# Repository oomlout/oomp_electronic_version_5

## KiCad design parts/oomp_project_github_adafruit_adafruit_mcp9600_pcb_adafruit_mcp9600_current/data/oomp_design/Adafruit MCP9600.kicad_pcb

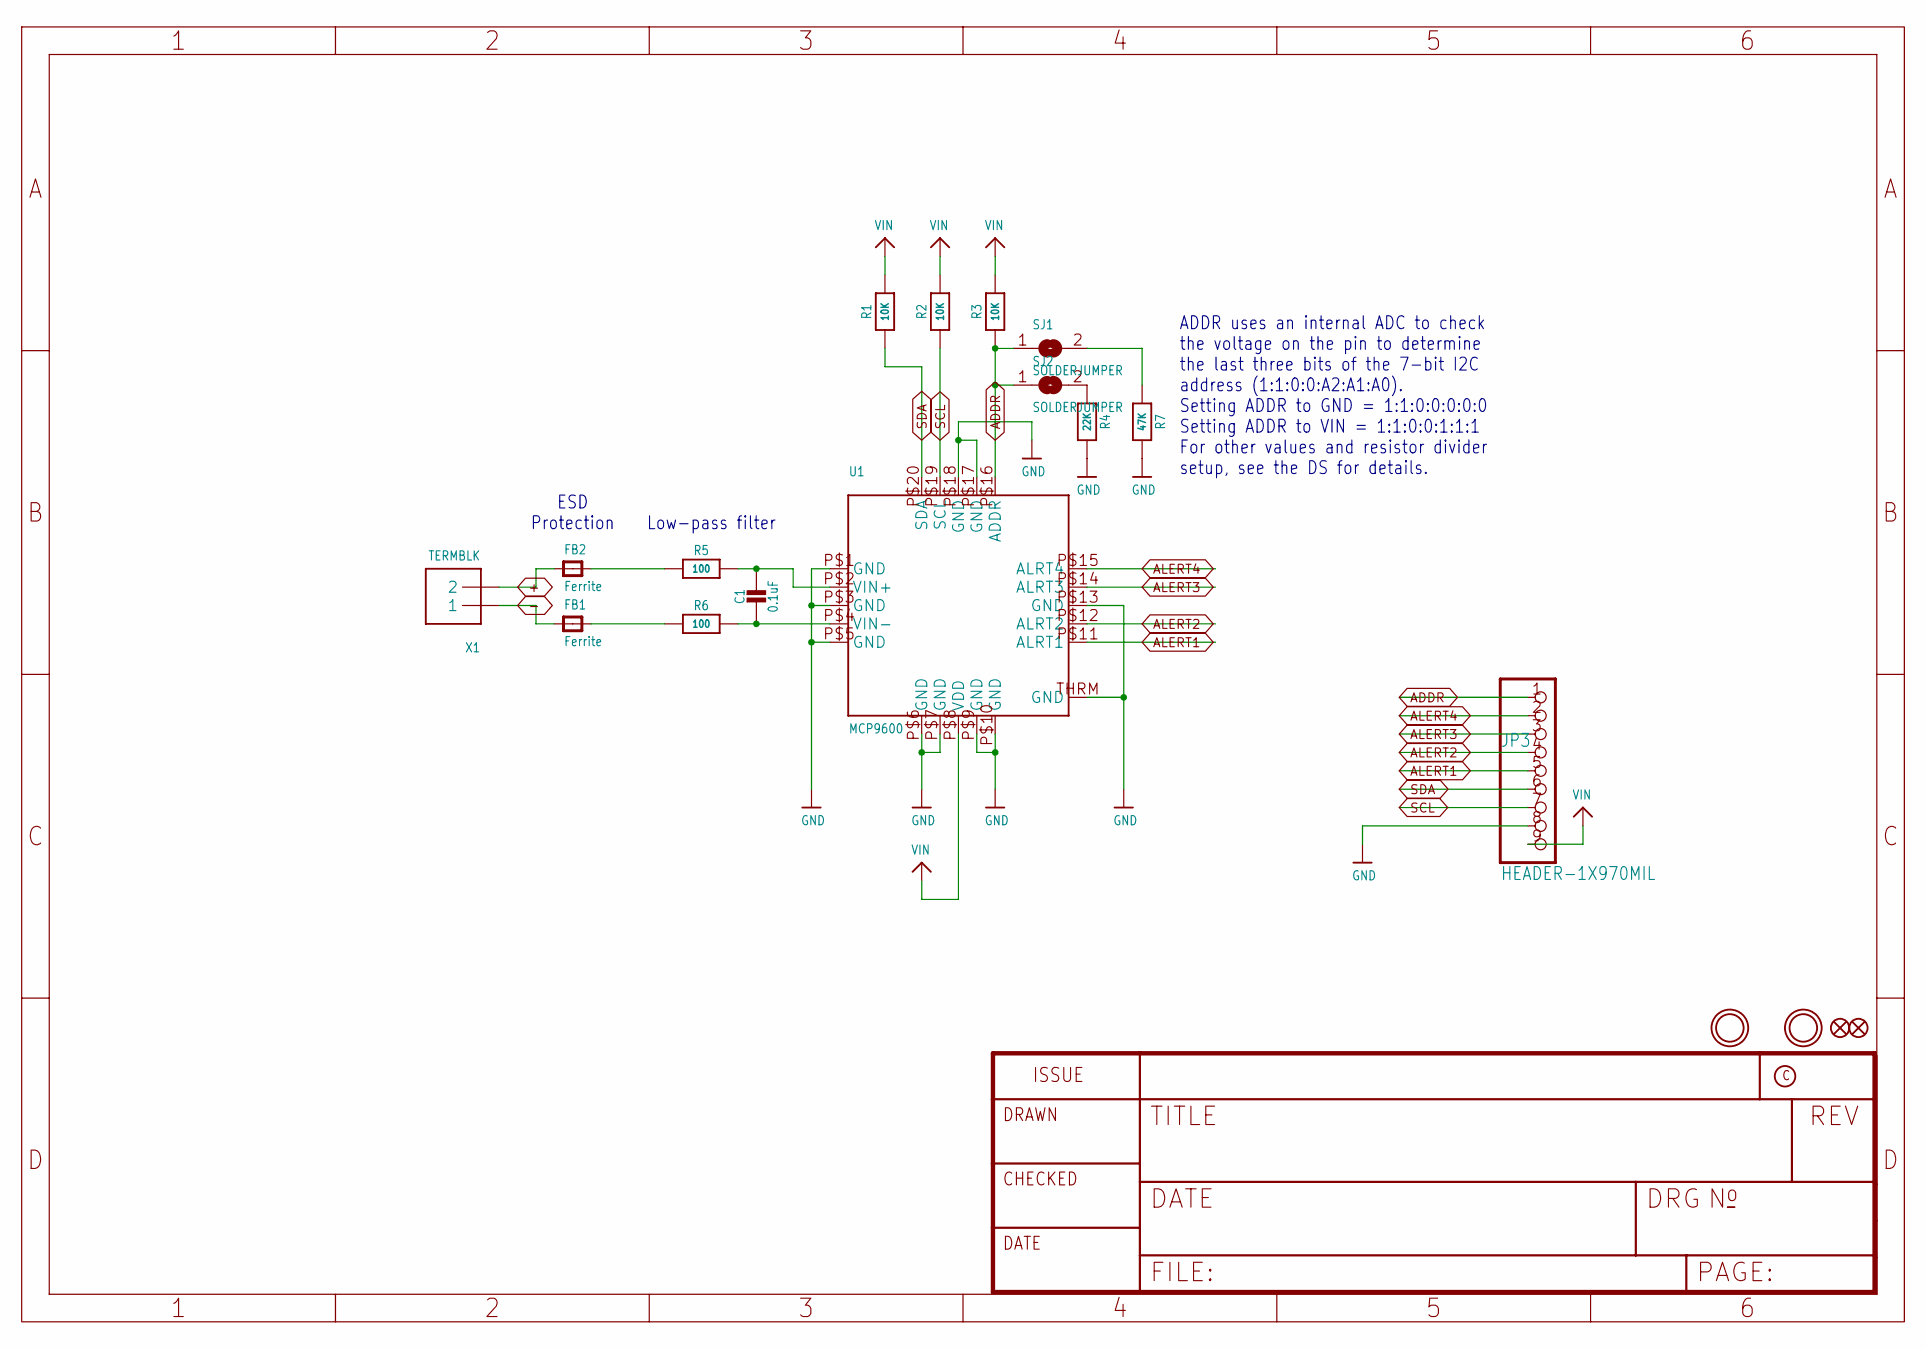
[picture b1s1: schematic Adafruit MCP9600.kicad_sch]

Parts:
C1: 0.1uF; 0603-NO
FB1, FB2: Ferrite; 0805-NO
FID1, FID2: FIDUCIAL_1MM
JP3: HEADER-1X970MIL; 1X09_ROUND_70
R1, R2, R3: 10K; 0603-NO
R4: 22K; 0603-NO
R5, R6: 100; 0603-NO
R7: 47K; 0603-NO
SJ1, SJ2: SOLDERJUMPER; SOLDERJUMPER_ARROW_NOPASTE
U1: MCP9600; VQFN20_5MM
U$1, U$3: MOUNTINGHOLE2.5; MOUNTINGHOLE_2.5_PLATED
X1: TERMBLK; TERMBLOCK_1X2-3.5MM

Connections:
+: FB2.1, X1.2
-: FB1.1, X1.1
ADDR: JP3.1, R3.1, SJ1.1, SJ2.1, U1.P$16 (ADDR)
ALERT1: JP3.5, U1.P$11 (ALRT1)
ALERT2: JP3.4, U1.P$12 (ALRT2)
ALERT3: JP3.3, U1.P$14 (ALRT3)
ALERT4: JP3.2, U1.P$15 (ALRT4)
GND: JP3.8, R4.2, R7.2, U1.P$1 (GND), U1.P$3 (GND), U1.P$5 (GND), U1.P$6 (GND), U1.P$7 (GND), U1.P$9 (GND), U1.P$10 (GND), U1.P$13 (GND), U1.P$17 (GND), U1.P$18 (GND), U1.THRM (GND)
unnamed: C1.1, R5.2, U1.P$2 (VIN+)
unnamed: C1.2, R6.2, U1.P$4 (VIN-)
unnamed: FB1.2, R6.1
unnamed: FB2.2, R5.1
unnamed: R7.1, SJ1.2
unnamed: R4.1, SJ2.2
SCL: JP3.7, R2.1, U1.P$19 (SCL)
SDA: JP3.6, R1.1, U1.P$20 (SDA)
VIN: JP3.9, R1.2, R2.2, R3.2, U1.P$8 (VDD)

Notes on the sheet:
ESD Protection
ADDR uses an internal ADC to check the voltage on the pin to determine the last three bits of the 7-bit I2C address (1:1:0:0:A2:A1:A0). Setting ADDR to GND = 1:1:0:0:0:0:0 Setting ADDR to VIN = 1:1:0:0:1:1:1 For other values and resistor divider setup, see the DS for details.
Low-pass filter

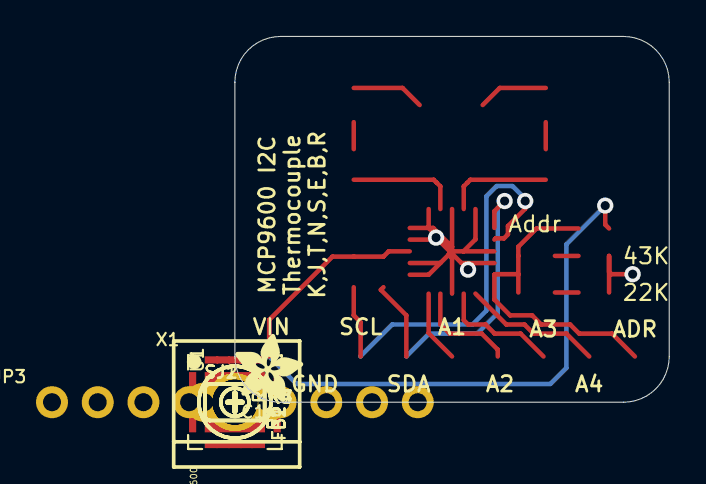
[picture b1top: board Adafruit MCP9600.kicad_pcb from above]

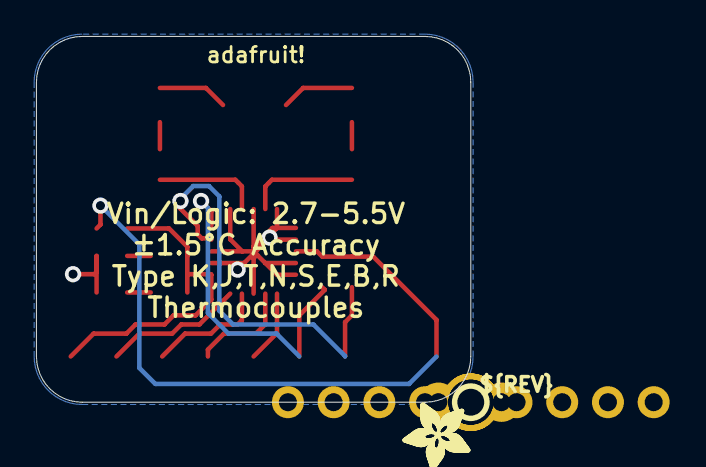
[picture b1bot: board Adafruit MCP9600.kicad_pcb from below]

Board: 2 copper layers, 24.1 x 20.3 mm, 25 parts (3 on the bottom side), 17 nets.

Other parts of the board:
U$16, U$19, U$20: ADAFRUIT_3.5MM
U$17: SYMBOL_PLUS
U$18: SYMBOL_MINUS
U$21: PCBFEAT-REV-040

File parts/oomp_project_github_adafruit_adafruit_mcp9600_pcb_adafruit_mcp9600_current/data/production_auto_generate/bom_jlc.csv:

Comment,Designator,Footprint,LCSC Part #
,JP3,Adafruit MCP9600-import-fps:1X09_ROUND_70,C2932701
,"U$16,U$19,U$20",Adafruit MCP9600-import-fps:ADAFRUIT_3.5MM,
,U$21,Adafruit MCP9600-import-fps:PCBFEAT-REV-040,
,U$18,Adafruit MCP9600-import-fps:SYMBOL_MINUS,
,U$17,Adafruit MCP9600-import-fps:SYMBOL_PLUS,
0.1uF,C1,Adafruit MCP9600-import-fps:0603-NO,C14663
100,"R5,R6",Adafruit MCP9600-import-fps:0603-NO,C22775
10K,"R1,R2,R3",Adafruit MCP9600-import-fps:0603-NO,C98220
22K,R4,Adafruit MCP9600-import-fps:0603-NO,C31850
47K,R7,Adafruit MCP9600-import-fps:0603-NO,C2907042
Ferrite,"FB1,FB2",Adafruit MCP9600-import-fps:0805-NO,
MCP9600,U1,Adafruit MCP9600-import-fps:VQFN20_5MM,
TERMBLK,X1,Adafruit MCP9600-import-fps:TERMBLOCK_1X2-3.5MM,

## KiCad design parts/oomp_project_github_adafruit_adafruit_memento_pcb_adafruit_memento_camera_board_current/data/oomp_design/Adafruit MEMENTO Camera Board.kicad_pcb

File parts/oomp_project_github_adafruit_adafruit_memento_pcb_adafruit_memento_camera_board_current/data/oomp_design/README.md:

# OOMP KiCad design copy

Open `Adafruit MEMENTO Camera Board.kicad_pro` (or the `.kicad_pcb` / `.kicad_sch`) in KiCad. Local OOMP libraries are under `libraries/`. Original inputs are preserved in [../original/](../original/).

Only verified unchanged installed KiCad defaults were renamed. Modified, custom, unmatched and unavailable items remain unchanged. Soldering variants are never swapped during conversion. Existing pad coordinates, nets and UUIDs are preserved.

See [conversion_report.yaml](conversion_report.yaml) for every conversion and skip. Copy this directory before editing; regeneration refuses to overwrite edited design files.

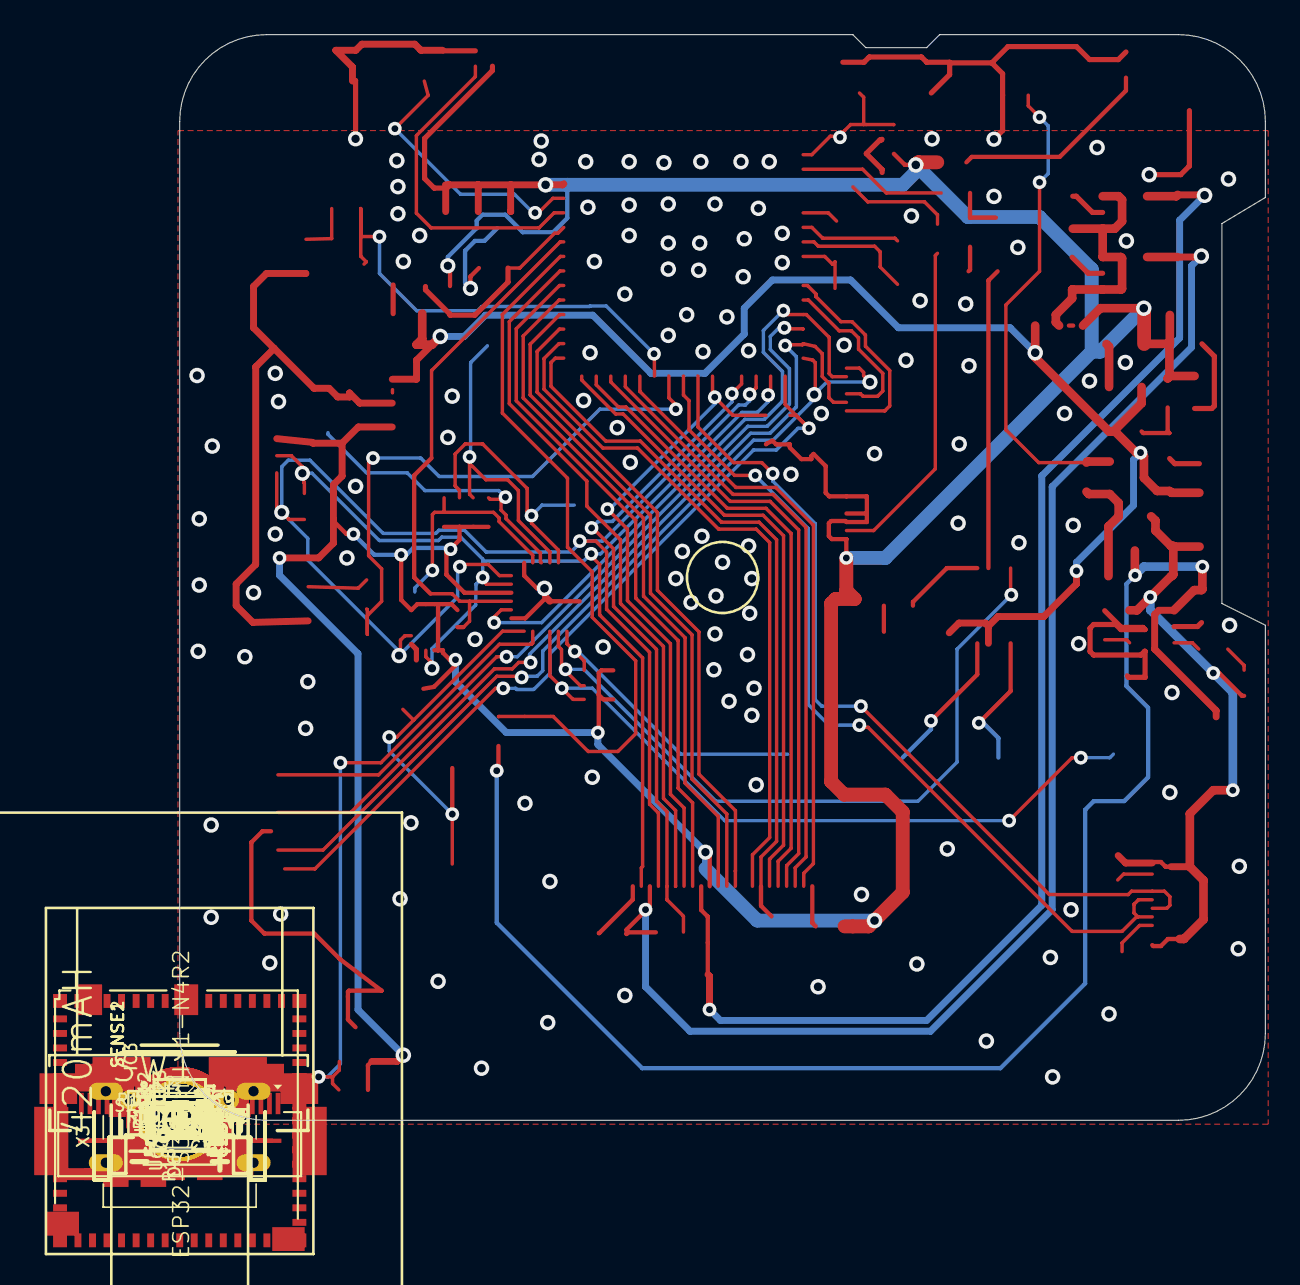
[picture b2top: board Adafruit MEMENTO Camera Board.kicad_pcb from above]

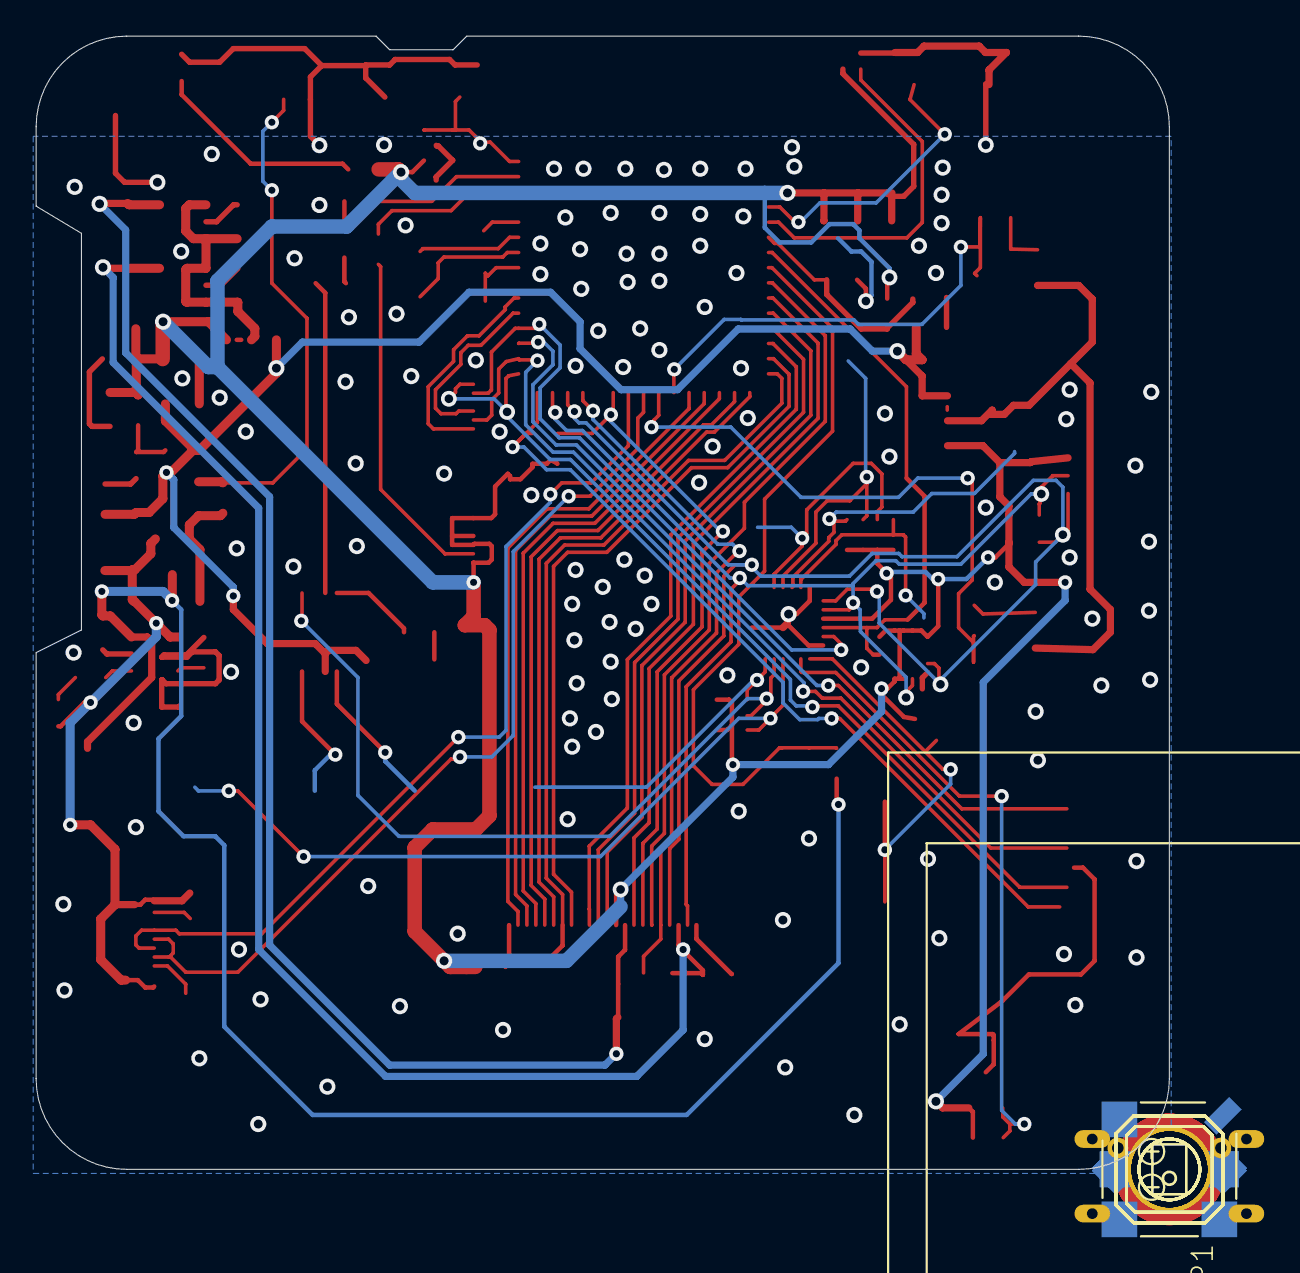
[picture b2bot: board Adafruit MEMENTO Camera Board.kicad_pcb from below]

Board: 2 copper layers, 63.5 x 63.5 mm, 125 parts (12 on the bottom side), 81 nets.

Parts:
C1, C3, C4, C7, C8, C9, C10, C11, C13, C17, C18, C19, C20, C22, C23, C29, C30, C32, C33, C34, C35, C36, C38: 10uF; 0805-NO
C2, C5, C15, C16, C25, C27, C31, C37, C39, C40, C41: 0.1uF; 0603-NO
C6, C12, C14, C28: 1uF; 0603-NO
C21: 0.01uF; 0603-NO
C26: 22pF; 0603-NO
CHG1: ORANGE; CHIPLED_0603_NOOUTLINE
CONN1: STEMMA_I2C_QT; JST_SH4
D1, D6: 3.6V; SOD-323
D4: 1N5819; SOD-123
DOWN0: TL9210
FB1: ferrite; 0603-NO
IC2: TLV62569; SOT23-5
IC3: AW9523; QFN24_4MM_SMSC
IC4: LIS3DH; LGA16_3X3MM
JP2: UART; 1X02_ROUND
L2: 2.2uH/NRH2412T2R2MNGH; INDUCTOR_TAIYOYUDEN_NR3015
LED2: WS2812B_SK6805_1515; SK6805_1515
LEFT0: TL9210
OK0: TL9210
ON0: GREEN; CHIPLED_0603_NOOUTLINE
Q1, Q3, Q4: AO3401; SOT23-R
Q2: BSS138; SOT23-WIDE
R1, R5, R7, R15, R21, R26: 10K; 0603-NO
R2, R3, R4, R8: 5.1K; 0603-NO
R6, R9, R12, R14, R23, R27, R28, R29, R30: 47K; 0603-NO
R10, R11, R17: 1Meg; 0603-NO
R13, R20: 10K Pack; RESPACK_4X0603
R16, R18, R19: 1K; 0603-NO
R22: 22; 0603-NO
R24: 450K; 0603-NO
R25: 100K; 0603-NO
RIGHT0: TL9210
SELECT0: TL9210
SENSE1, SENSE2: JST PH 3; JSTPH3
SJ1, SJ2: SOLDERJUMPER_2WAY_OPEN_NOPASTE
SJ3: SOLDERJUMPER_CLOSEDWIRE
SP1: 7.5mm SPK; BUZZER_SMT_7.5MM
SW1, SW2: RA_TACT; SPST_TACTILE_RA
SW4: SPDT R/A; SPDT_SMT_SSSS811101
TFT1: DISP_TFT_1.54IN_240X240_22P; TFT_1.54IN_240X240_22PIN
TP1, TP2, TP7, TP8: TESTPOINT_ROUND_1.5MM_NO
TP3, TP4, TP5, TP6: SEWTAP_SMTNUTM3; SMT_NUT_3MM
U1: TLV74328; SOT23-5
U2: MCP73831T-2ACI/OT; SOT23-5
U3: ESP32-S3-MINI-1-N4R2; ESP32-S2-MINI-1
U5: TLV74315; SOT23-5
U6: PAM8302; MSOP8_0.65MM
U7: Microphone; MEMS_MIC_2.75X1.85
U$83: LIPO_552535
U$119: MEMENTO_TOP
U$120: MEMENTO_BOT
U$121: PCBFEAT-REV-040
UP0: TL9210
X1: JST PH 2; JSTPH2_BATT
X2: CAMERA_OV2640; OV2640FSL
X3: MicroSD; MICROSD
X4: USB C; USB_C_CUSB31-CFM2AX-01-X

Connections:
1.5V: C27.1, C28.1, C32.1, C33.1, U5.5, X2.10
2.8V: C22.1, C25.1, C29.1, U1.5, X2.4
3.3V: C2.1, C4.1, C5.1, C7.1, C9.2, C10.1, C13.1, C17.1, C18.1, C34.1, C35.1, C36.1, CONN1.2, IC3.21, IC4.1, IC4.7, IC4.8, IC4.13, IC4.14, IC4.15, IC4.16, L2.P$2, LED2.2, Q4.2, R1.2, R5.1, R6.2, R7.1, R9.2, R13.5, R13.6, R13.7, R13.8, R15.2, R20.6, R20.8, R23.2, R24.2, R26.1, R28.2, SJ1.1, SJ2.3, SJ3.2, TFT1.1, TFT1.3, TFT1.4, TFT1.6, U3.3, U7.1, X2.11
A1_JST1: R18.1, SENSE1.3
AD0: D1.C, R16.2, U3.21
AD1: D6.C, R18.2, U3.22
AGND: FB1.2, X2.2
BACKLIGHT: Q2.1, U3.41
BATT_MON: C16.1, R10.2, R11.1, U3.8
BOOT0/SHUTTER: SW1.1, TP1.P$1, TP8.P$1, U3.4
BUTTONOK: IC3.4, OK0.2, R20.3
BUTTONSEL: IC3.6, R20.1, SELECT0.2
CAM_PWDN: R28.1, U3.25, X2.8
CAM_RST: R27.1, U3.27, X2.6
CARDDET: IC3.1, R23.1, X3.CD1, X3.CD2
CARD_CS: R15.1, U3.30, X3.2
CC1: R8.2, X4.A5
CC2: R3.2, X4.B5
D10_JST: R16.1, SENSE2.3
D+: U3.24, X4.A6, X4.B6
D-: U3.23, X4.A7, X4.B7
DATA1: SJ3.1, X2.23
DATA2: U3.17, X2.19
DATA3: U3.19, X2.21
DATA4: U3.20, X2.22
DATA5: U3.18, X2.20
DATA6: U3.16, X2.18
DATA7: U3.14, X2.16
DATA8: U3.13, X2.14
DATA9: U3.11, X2.12
DOWN: DOWN0.2, IC3.17, R13.4
EN: Q3.1, R12.2, SW4.B
EXT_XCLK: U3.12, X2.13
FB: IC2.5, R24.1, R25.2
GND: C1.2, C2.2, C3.2, C4.2, C5.2, C6.2, C7.2, C8.2, C9.1, C10.2, C11.2, C12.2, C13.2, C14.2, C15.2, C16.2, C17.2, C18.2, C19.2, C20.2, C21.1, C22.2, C23.2, C25.2, C26.2, C27.2, C28.2, C29.2, C30.2, C31.2, C32.2, C33.2, C34.2, C35.2, C36.2, C37.2, C38.1, C40.2, CONN1.1, CONN1.MT1, CONN1.MT2, D1.A, D6.A, DOWN0.1, FB1.1, IC2.2, IC3.9, IC3.18, IC3.24, IC3.THERM, IC4.5, IC4.10, IC4.12, LED2.4, LEFT0.1, OK0.1, ON0.C, Q2.2, R2.1, R3.1, R8.1, R11.2, R14.1, R17.1, R20.7, R21.1, R25.1, R27.2, RIGHT0.1, SELECT0.1, SENSE1.1, SENSE1.NC1, SENSE1.NC2, SENSE2.1, SENSE2.NC1, SENSE2.NC2, SW1.2, SW1.MT1, SW1.MT2, SW2.1, SW2.MT1, SW2.MT2, SW4.C, TFT1.5, TFT1.7, TFT1.8, TFT1.9, TFT1.10, TFT1.11, TFT1.12, TFT1.13, TFT1.14, TFT1.15, TFT1.22, TFT1.SUPPORT1, TFT1.SUPPORT2, TP3.P$1, TP4.P$1, TP5.P$1, TP6.P$1, U1.2, U2.2, U3.1, U3.2, U3.42, U3.43, U3.46, U3.47, U3.48, U3.49, U3.50, U3.51, U3.52, U3.53, U3.54, U3.55, U3.56, U3.57, U3.58, U3.59, U3.60, U3.61, U3.62, U3.63, U3.64, U3.65, U3.66, U3.67, U3.68, U3.69, U3.70, U3.71, U3.72, U3.73, U5.2, U6.7, U7.2, U7.3, UP0.1, X1.1, X1.NC1, X1.NC2, X2.15, X2.SPRT1, X2.SPRT2, X3.6, X3.MT1, X3.MT2, X4.A1B12, X4.B1A12
HSYNC: U3.10, X2.9
IO42_DBLTAP: C6.1, R17.2, U3.38
IRQ: IC3.22, IC4.11, U3.7
LED_K: R22.1, TFT1.2
LEFT: IC3.16, LEFT0.2, R13.1
MIC: C41.2, R9.1, R21.2, U3.6
MISO: U3.33, X3.7
MOSI: TFT1.21, U3.31, X3.3
unnamed: C41.1, U7.4
unnamed: ON0.A, R6.1
unnamed: R4.1, U2.1
unnamed: Q2.3, R22.2
unnamed: CHG1.C, R4.2
unnamed: R29.2, U6.4
unnamed: R30.2, U6.3
unnamed: R2.2, U2.5
unnamed: C40.1, R29.1
unnamed: SP1.-, U6.8
unnamed: SP1.+, U6.5
unnamed: C39.1, R30.1
unnamed: C21.2, C39.2, R19.1
unnamed: IC2.3, L2.P$1
unnamed: D4.C, Q1.2, Q3.2, R12.1
NEOPIXEL: LED2.1, U3.5
PCLK: C26.1, U3.15, X2.17
PERIPH_RST: IC3.23, TFT1.20, U3.34
RESET: C14.1, R1.1, SW2.2, TP2.P$1, TP7.P$1, U3.45
RIGHT: IC3.14, R13.3, RIGHT0.2
RXD0: JP2.2, U3.40
SCK: TFT1.17, U3.32, X3.5
SCL: CONN1.4, IC3.19, IC4.4, R5.2, U3.28, X2.5
SDA: CONN1.3, IC3.20, IC4.6, R7.2, U3.29, X2.3
SD_PWR: IC3.2, Q4.1, R26.2
SD_VDD: C37.1, C38.2, Q4.3, X3.4
SPKR: R19.2, U3.44
SPKR_SD: IC3.5, R20.2, U6.1
TFT_CS: TFT1.18, U3.35
TFT_DC: TFT1.16, U3.36
TXD0: JP2.1, U3.39
UP: IC3.15, R13.2, UP0.2
VBAT: C8.1, Q1.3, R10.1, U2.3, X1.2
VBUS: C1.1, C15.1, CHG1.A, D4.A, Q1.1, R14.2, U2.4, X4.A4B9, X4.B4A9
VCC: C20.1, SENSE1.2, SENSE2.2, SJ2.2
VHIGH: C3.1, C11.1, C12.1, C30.1, C31.1, IC2.1, IC2.4, Q3.3, SJ1.3, SJ2.1, U6.6
VPWR: C19.1, C23.1, SJ1.2, U1.1, U1.3, U5.1, U5.3
VSYNC: U3.9, X2.7

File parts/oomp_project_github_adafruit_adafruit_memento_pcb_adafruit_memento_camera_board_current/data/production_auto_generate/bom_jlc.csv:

Comment,Designator,Footprint,LCSC Part #
,U$83,Adafruit MEMENTO Camera Board-import-fps:LIPO_552535,
,U$120,Adafruit MEMENTO Camera Board-import-fps:MEMENTO_BOT,
,U$119,Adafruit MEMENTO Camera Board-import-fps:MEMENTO_TOP,
,U$121,Adafruit MEMENTO Camera Board-import-fps:PCBFEAT-REV-040,
,"TP1,TP2,TP7,TP8",Adafruit MEMENTO Camera Board-import-fps:TESTPOINT_ROUND_1.5MM_NO,
0.01uF,C21,Adafruit MEMENTO Camera Board-import-fps:0603-NO,C5137477
0.1uF,"C2,C5,C15,C16,C25,C27,C31,C37,C39,C40,C41",Adafruit MEMENTO Camera Board-import-fps:0603-NO,C14663
100K,R25,Adafruit MEMENTO Camera Board-import-fps:0603-NO,C25803
10K,"R1,R5,R7,R15,R21,R26",Adafruit MEMENTO Camera Board-import-fps:0603-NO,C98220
10K Pack,"R13,R20",Adafruit MEMENTO Camera Board-import-fps:RESPACK_4X0603,C98220
10uF,"C1,C3,C4,C7,C8,C9,C10,C11,C13,C17,C18,C19,C20,C22,C23,C29,C30,C32,C33,C34,C35,C36,C38",Adafruit MEMENTO Camera Board-import-fps:0805-NO,
1K,"R16,R18,R19",Adafruit MEMENTO Camera Board-import-fps:0603-NO,C2907002
1Meg,"R10,R11,R17",Adafruit MEMENTO Camera Board-import-fps:0603-NO,C2907003
1N5819,D4,Adafruit MEMENTO Camera Board-import-fps:SOD-123,
1uF,"C6,C12,C14,C28",Adafruit MEMENTO Camera Board-import-fps:0603-NO,C5673
2.2uH/NRH2412T2R2MNGH,L2,Adafruit MEMENTO Camera Board-import-fps:INDUCTOR_TAIYOYUDEN_NR3015,
22,R22,Adafruit MEMENTO Camera Board-import-fps:0603-NO,C23345
22pF,C26,Adafruit MEMENTO Camera Board-import-fps:0603-NO,C105620
3.6V,"D1,D6",Adafruit MEMENTO Camera Board-import-fps:SOD-323,
450K,R24,Adafruit MEMENTO Camera Board-import-fps:0603-NO,
47K,"R6,R9,R12,R14,R23,R27,R28,R29,R30",Adafruit MEMENTO Camera Board-import-fps:0603-NO,C2907042
5.1K,"R2,R3,R4,R8",Adafruit MEMENTO Camera Board-import-fps:0603-NO,C23186
7.5mm SPK,SP1,Adafruit MEMENTO Camera Board-import-fps:BUZZER_SMT_7.5MM,
AO3401,"Q1,Q3,Q4",Adafruit MEMENTO Camera Board-import-fps:SOT23-R,
AW9523,IC3,Adafruit MEMENTO Camera Board-import-fps:QFN24_4MM_SMSC,
BSS138,Q2,Adafruit MEMENTO Camera Board-import-fps:SOT23-WIDE,C52895
CAMERA_OV2640,X2,Adafruit MEMENTO Camera Board-import-fps:OV2640FSL,
DISP_TFT_1.54IN_240X240_22P,TFT1,Adafruit MEMENTO Camera Board-import-fps:TFT_1.54IN_240X240_22PIN,
ESP32-S3-MINI-1-N4R2,U3,Adafruit MEMENTO Camera Board-import-fps:ESP32-S2-MINI-1,
ferrite,FB1,Adafruit MEMENTO Camera Board-import-fps:0603-NO,
GREEN,ON0,Adafruit MEMENTO Camera Board-import-fps:CHIPLED_0603_NOOUTLINE,
JST PH 2,X1,Adafruit MEMENTO Camera Board-import-fps:JSTPH2_BATT,
JST PH 3,"SENSE1,SENSE2",Adafruit MEMENTO Camera Board-import-fps:JSTPH3,
LIS3DH,IC4,Adafruit MEMENTO Camera Board-import-fps:LGA16_3X3MM,
MCP73831T-2ACI/OT,U2,Adafruit MEMENTO Camera Board-import-fps:SOT23-5,
Microphone,U7,Adafruit MEMENTO Camera Board-import-fps:MEMS_MIC_2.75X1.85,
MicroSD,X3,Adafruit MEMENTO Camera Board-import-fps:MICROSD,
ORANGE,CHG1,Adafruit MEMENTO Camera Board-import-fps:CHIPLED_0603_NOOUTLINE,
PAM8302,U6,Adafruit MEMENTO Camera Board-import-fps:MSOP8_0.65MM,
RA_TACT,"SW1,SW2",Adafruit MEMENTO Camera Board-import-fps:SPST_TACTILE_RA,
SPDT R/A,SW4,Adafruit MEMENTO Camera Board-import-fps:SPDT_SMT_SSSS811101,
STEMMA_I2C_QT,CONN1,Adafruit MEMENTO Camera Board-import-fps:JST_SH4,C160404
TL9210,"DOWN0,LEFT0,OK0,RIGHT0,SELECT0,UP0",Adafruit MEMENTO Camera Board-import-fps:TL9210,
TLV62569,IC2,Adafruit MEMENTO Camera Board-import-fps:SOT23-5,
TLV74315,U5,Adafruit MEMENTO Camera Board-import-fps:SOT23-5,
TLV74328,U1,Adafruit MEMENTO Camera Board-import-fps:SOT23-5,
UART,JP2,Adafruit MEMENTO Camera Board-import-fps:1X02_ROUND,C492401
USB C,X4,Adafruit MEMENTO Camera Board-import-fps:USB_C_CUSB31-CFM2AX-01-X,
WS2812B_SK6805_1515,LED2,Adafruit MEMENTO Camera Board-import-fps:SK6805_1515,

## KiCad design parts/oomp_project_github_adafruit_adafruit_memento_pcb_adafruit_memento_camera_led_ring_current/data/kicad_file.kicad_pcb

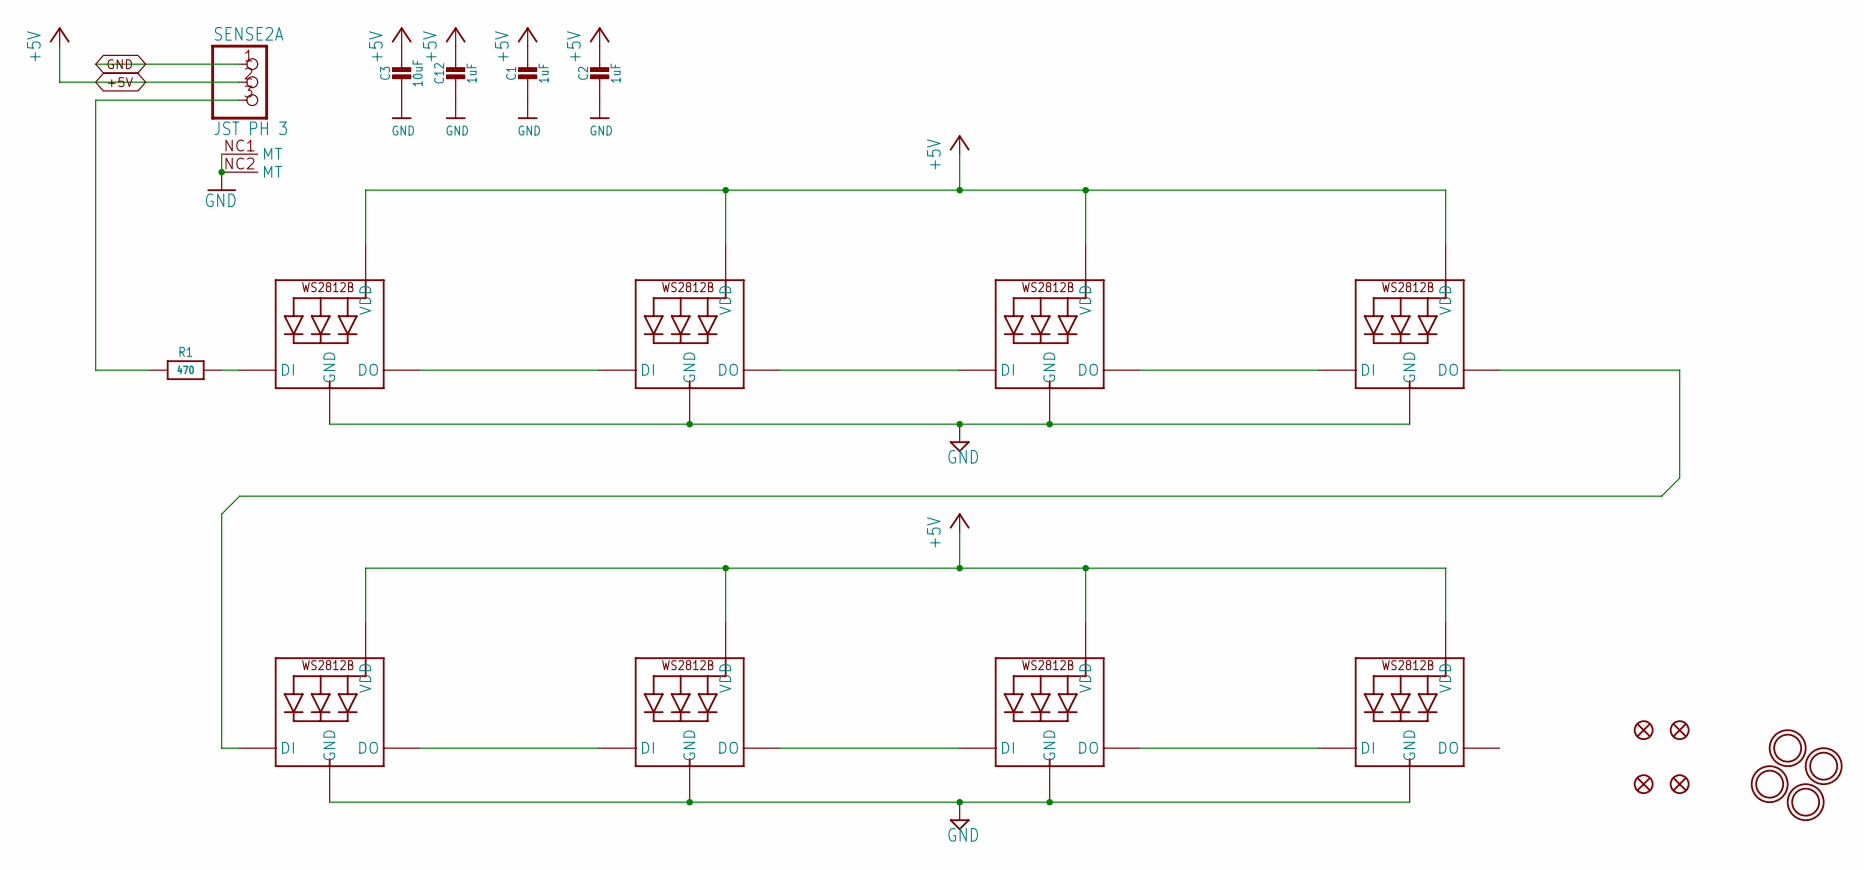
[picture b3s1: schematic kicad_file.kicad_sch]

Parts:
C1, C2, C12: 1uF; 0603-NO
C3: 10uF; 0805-NO
FID1, FID2, FID3, FID4: FIDUCIAL_1MM
LED1, LED3, LED5, LED7, LED9, LED11, LED13, LED15: WS2812B_5050N; WS2812B-NARROW
R1: 470; 0603-NO
SENSE2: JST PH 3; JSTPH3
U$1, U$2, U$3, U$4: MOUNTINGHOLE3.0THIN; MOUNTINGHOLE_3.0_PLATEDTHIN

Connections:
+5V: C1.1, C2.1, C3.1, C12.1, LED1.1-VDD (VDD), LED3.1-VDD (VDD), LED5.1-VDD (VDD), LED7.1-VDD (VDD), LED9.1-VDD (VDD), LED11.1-VDD (VDD), LED13.1-VDD (VDD), LED15.1-VDD (VDD), SENSE2.2
GND: C1.2, C2.2, C3.2, C12.2, LED1.3-GND (GND), LED3.3-GND (GND), LED5.3-GND (GND), LED7.3-GND (GND), LED9.3-GND (GND), LED11.3-GND (GND), LED13.3-GND (GND), LED15.3-GND (GND), SENSE2.1, SENSE2.NC1 (MT), SENSE2.NC2 (MT)
IN: R1.1, SENSE2.3
unnamed: LED1.2-DOUT (DO), LED3.4-DIN (DI)
unnamed: LED3.2-DOUT (DO), LED5.4-DIN (DI)
unnamed: LED5.2-DOUT (DO), LED7.4-DIN (DI)
unnamed: LED9.2-DOUT (DO), LED11.4-DIN (DI)
unnamed: LED11.2-DOUT (DO), LED13.4-DIN (DI)
unnamed: LED13.2-DOUT (DO), LED15.4-DIN (DI)
unnamed: LED7.2-DOUT (DO), LED9.4-DIN (DI)
unnamed: LED1.4-DIN (DI), R1.2

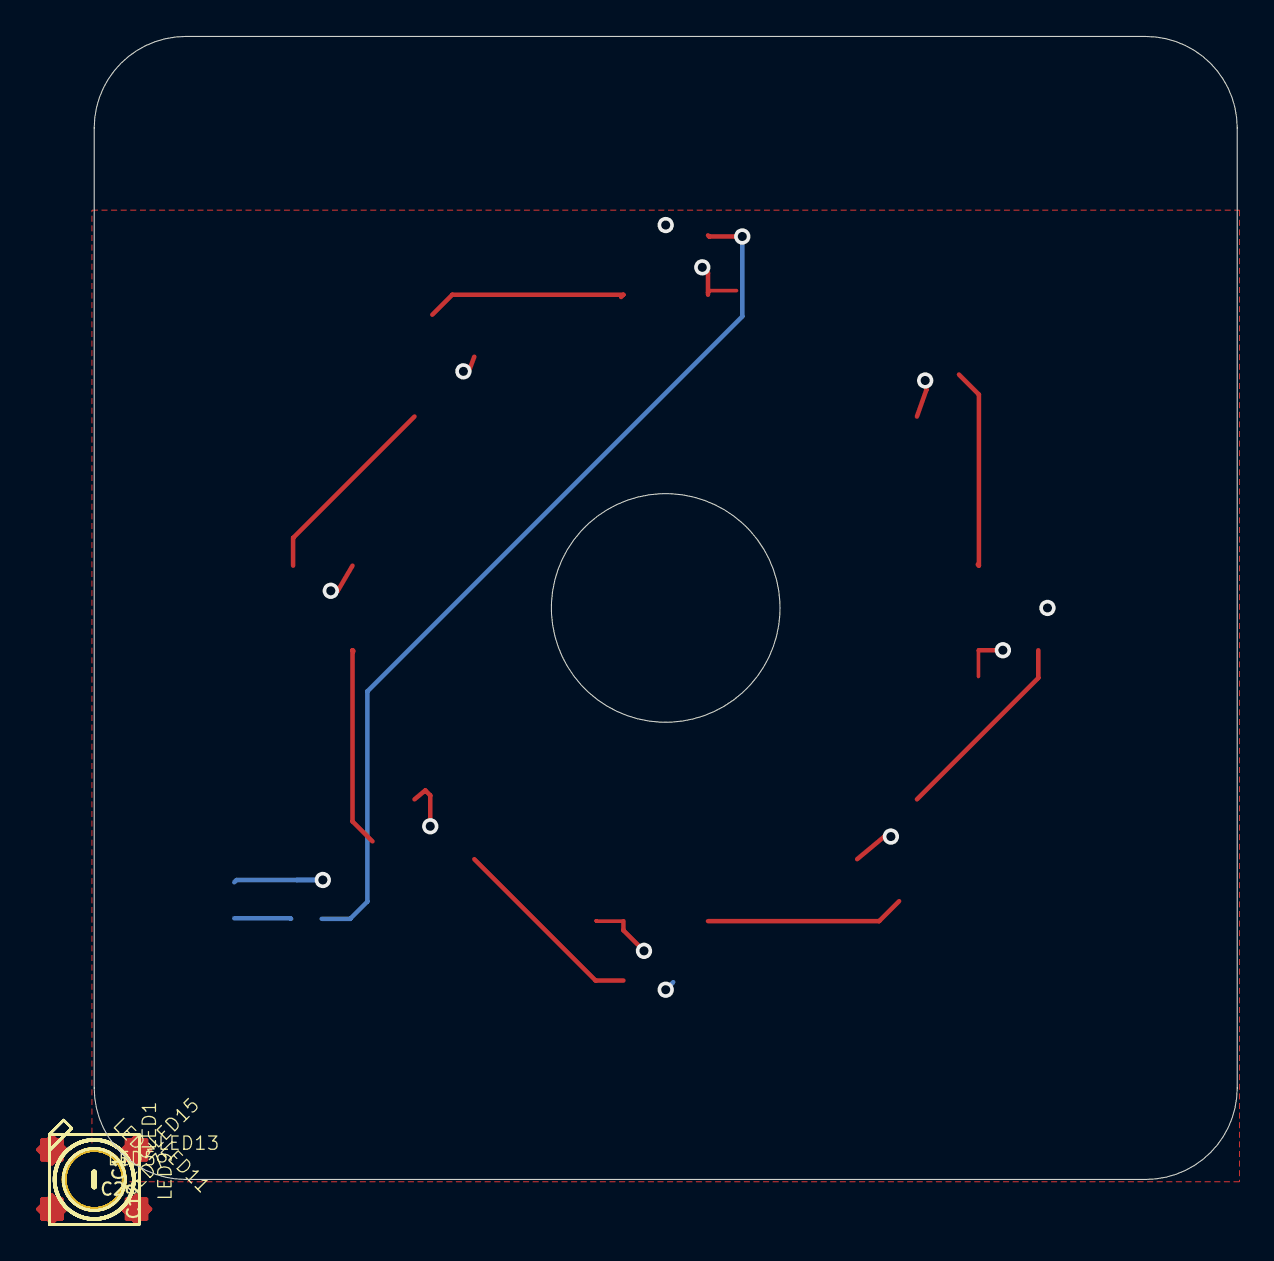
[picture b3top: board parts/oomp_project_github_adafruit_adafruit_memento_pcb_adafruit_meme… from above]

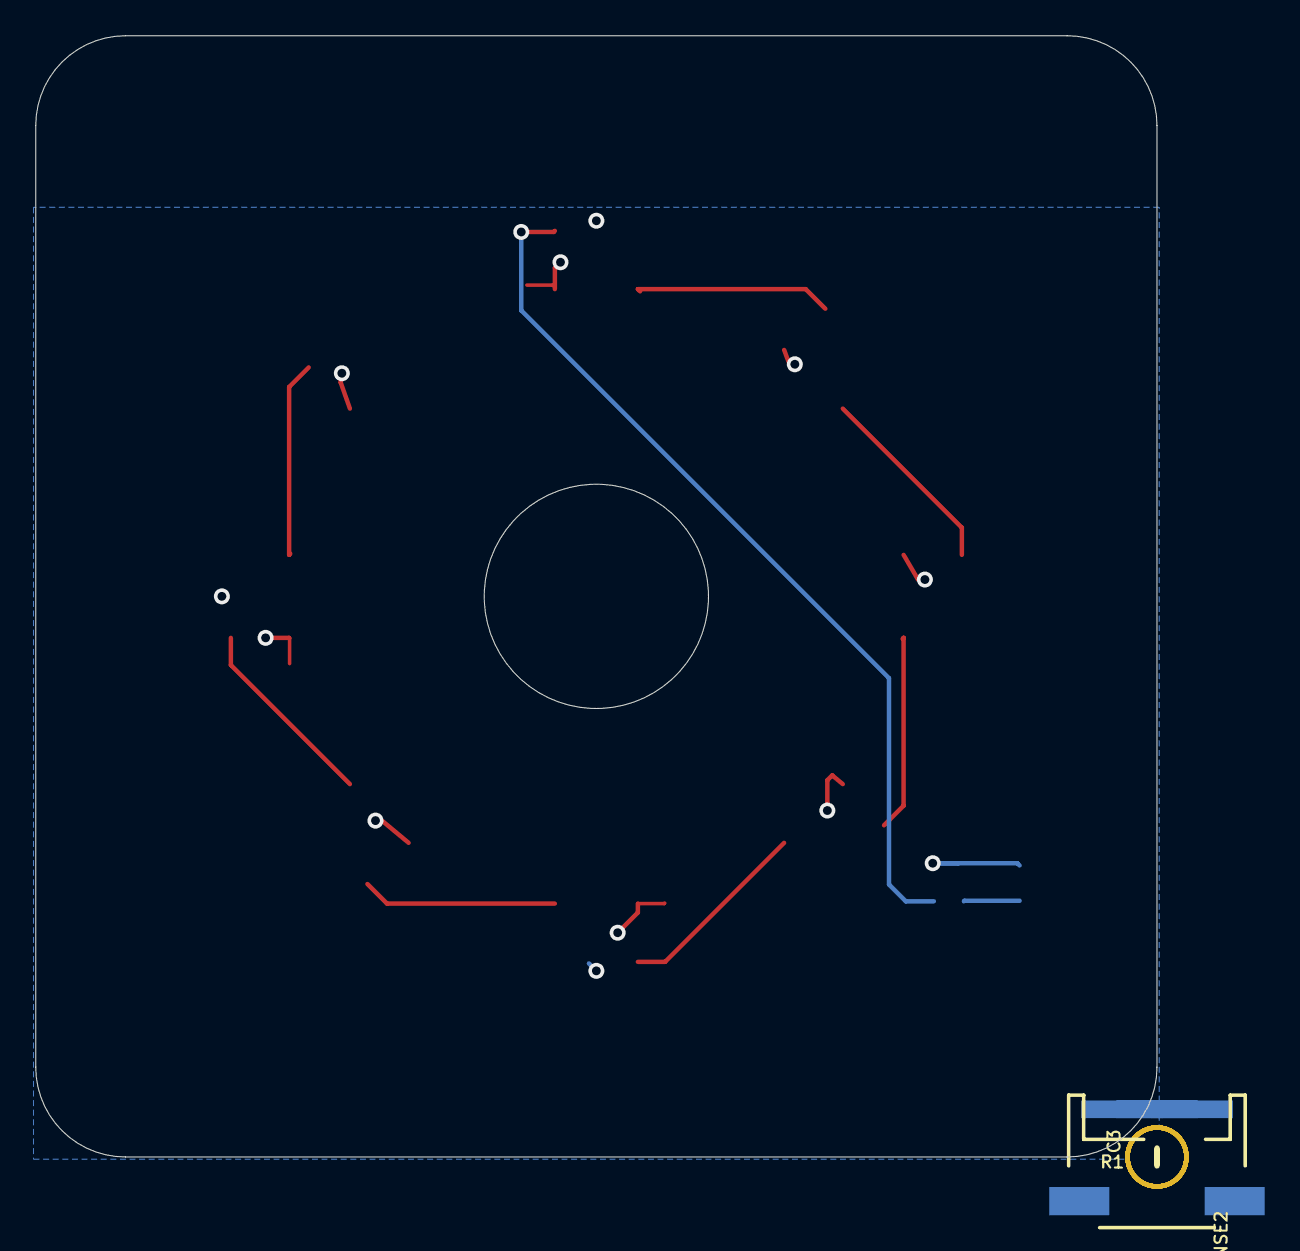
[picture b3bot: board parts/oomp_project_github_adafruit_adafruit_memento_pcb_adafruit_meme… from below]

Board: 2 copper layers, 63.5 x 63.5 mm, 24 parts (6 on the bottom side), 11 nets.

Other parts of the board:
U$8: MEMENTO_LED_BOT
U$9: MEMENTO_LED_TOP

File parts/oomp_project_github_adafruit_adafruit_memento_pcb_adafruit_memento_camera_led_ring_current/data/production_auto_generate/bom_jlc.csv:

Comment,Designator,Footprint,LCSC Part #
,U$8,Adafruit MEMENTO Camera LED Ring-import-fps:MEMENTO_LED_BOT,
,U$9,Adafruit MEMENTO Camera LED Ring-import-fps:MEMENTO_LED_TOP,
10uF,C3,Adafruit MEMENTO Camera LED Ring-import-fps:0805-NO,
1uF,"C1,C2,C12",Adafruit MEMENTO Camera LED Ring-import-fps:0603-NO,C5673
470,R1,Adafruit MEMENTO Camera LED Ring-import-fps:0603-NO,C23179
JST PH 3,SENSE2,Adafruit MEMENTO Camera LED Ring-import-fps:JSTPH3,
WS2812B_5050N,"LED1,LED3,LED5,LED7,LED9,LED11,LED13,LED15",Adafruit MEMENTO Camera LED Ring-import-fps:WS2812B-NARROW,

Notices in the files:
parts and their libraries:
COPYRIGHT: Copyright (C) 2018 Accelerated Designs. All rights reserved
